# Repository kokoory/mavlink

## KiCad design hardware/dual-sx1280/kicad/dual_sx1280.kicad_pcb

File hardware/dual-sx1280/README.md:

# Dual SX1280 초소형 보드 (NiceRF LoRa1280 ×2 + STM32F103)

NiceRF **LoRa1280 시리즈 데모보드**(SX1280 ranging demo board)의 구성(LoRa1280 모듈 + 48핀 STM32 계열 MCU + 3~12 V 입력)을
기준으로, **SX1280 모듈 두 개를 동시에 쓰는 20 × 33 mm 4층 양면 보드**로 다시 설계한 것입니다.

## 사양
| 항목 | 내용 |
|---|---|
| 크기 | 20.0 × 33.0 mm, 4층, 1.0 mm 두께 권장 |
| 무선 | NiceRF LoRa1280 ×2 (SX1280, 2.4 GHz LoRa/FLRC/GFSK/레인징, 최대 12.5 dBm) |
| 배치 | 무선 A(U1) 윗면, 무선 B(U2) 아랫면, 같은 위치에 겹쳐 실장 |
| 안테나 | 무선마다 U.FL 1개 (J1 윗면, J2 아랫면), 50 Ω CPWG 약 2.4 mm |
| MCU | STM32F103CBU6 (UFQFPN48, 128 KB), 크리스털 없음(HSI) |
| 무선 연결 | A = SPI1, B = SPI2, 각각 NSS/BUSY/DIO1/NRESET 독립 → 두 무선 동시 동작 |
| 호스트 | J3 JST-SH 1.0 mm 4핀: 1 = +5 V, 2 = TX(PA9), 3 = RX(PA10), 4 = GND |
| 전원 | 5 V 입력 → AP2112K-3.3 (600 mA) |
| 펌웨어 기록 | 아랫면 SWD 패드(SWDIO/SWCLK/NRST/3V3/GND) 또는 BOOT0 패드 + USART1 ROM 부트로더 |
| 표시 | LED 2개(아랫면): PA12 녹색(무선 A), PA15 파랑(무선 B). PA15는 JTDI 겸용이라 펌웨어에서 JTAG을 끄고 SWD만 켜야 합니다(SWJ_CFG=010) |

핀 정의는 [firmware/board_pins.h](firmware/board_pins.h)에 있습니다.

### LoRa1280 핀 (16핀, 2.0 mm 피치 캐스텔레이션, 16 × 16 mm)
`1 DIO2 · 2 DIO3 · 3 VCC · 4 GND · 5 MISO · 6 MOSI · 7 SCK · 8 NSS · 9 ANT · 10–12 GND · 13 NRESET · 14 GND(TCXO판은 TCXOEN) · 15 BUSY · 16 DIO1`

### JP1 / JP2 (모듈 14번 핀)
- 기본값은 1-2 브리지(GND)이며, 일반 **LoRa1280 / LoRa1281** 모듈에 맞습니다.
- **LoRa1280-T(TCXO)** 모듈을 쓸 때만 1-2 사이를 칼로 끊고 2-3을 납땜합니다. 그러면 3V3이 들어가 TCXO가 켜집니다.
- 일반 모듈에서 2-3을 연결하면 3V3이 GND에 단락됩니다.

## 디렉터리
| 경로 | 내용 |
|---|---|
| `scripts/design.py` | **설계 원본**: 부품, 좌표, 넷. 여기만 고치고 나머지는 재생성 |
| `scripts/gen_lib.py`, `gen_sch.py`, `gen_pcb.py` | 라이브러리 / 회로도 / PCB(배치·존·RF) 생성 |
| `scripts/route.py` | 자체 A* 자동배선기 (F.Cu / In2.Cu / B.Cu) |
| `scripts/check_netlist.py`, `drc.py` | 회로도·PCB 넷 대조, KiCad DRC |
| `scripts/export_fab.py` | 거버, 드릴, JLCPCB BOM/CPL, 미리보기 이미지 |
| `kicad/` | KiCad 7 프로젝트 (`dual_sx1280.kicad_pro/.kicad_sch/.kicad_pcb`) |
| `fab/` | 제조 파일 |
| `docs/` | 회로도 PDF/PNG, 레이어 이미지, DRC 리포트 |

## 확인이 필요한 가정
1. **데모보드 MCU 품번은 확인하지 못했습니다.** 공개 사진에서는 48핀 QFP라는 것만 보입니다. 그래서 STM32F103 계열로 가정했습니다.
   - 같은 48핀 STM32F103C8T6/CBT6(LQFP)와 핀 번호가 같습니다. 풋프린트만 바꾸면 그대로 쓸 수 있습니다.
   - 정확한 MCU는 NiceRF 데모 코드(`Lora1280 lora1281 Demo code.rar`)나 판매처에 문의해 확인하세요.
2. **LoRa1280 핀맵과 외형**은 NiceRF LoRa128X 데이터시트 Rev 2.2의 핀 표와 TinyGS의 NiceRF-1280 보드를 교차 확인한 것입니다.
   - 발주 전에 실제 모듈 데이터시트의 기구 도면과 패드 치수를 꼭 대조하세요.
3. **모듈 아래에도 트랙과 텐트 비아가 지나갑니다.** 모두 솔더마스크로 덮여 있습니다.
   - 모듈 밑면에 캐스텔레이션 외의 노출 구리가 있다면 그 부분을 비워야 합니다.
4. LCSC 품번은 일부만 넣었습니다. 비어 있는 품번과 재고는 직접 확인해야 합니다. MCU, LED, 모듈이 해당합니다.
5. LoRa1280 모듈은 JLC 부품이 아니어서 수납땜해야 합니다. BOM과 CPL에서도 빠져 있습니다.

## 검증 결과 (2026-11-12)
| 검사 | 결과 |
|---|---|
| 회로도 넷리스트와 `design.py` 대조 (`check_netlist.py sch`) | PASS, 넷 31개 |
| PCB 넷과 `design.py` 대조 (`check_netlist.py pcb`) | PASS |
| KiCad DRC (`drc.py`, 보고서 `docs/drc_report.txt`) | 오류 0, 미연결 0, 경고 4 |
| 코트야드 겹침 (앞·뒷면 각각) | 0 |

- 경고 4건은 모두 `starved_thermal`입니다. 서멀 스포크가 1개만 붙은 GND 패드라는 뜻이고, 연결 자체는 되어 있습니다.
- 배선 통계는 트랙 약 620 mm, 비아 219개입니다. 비아 중 112개는 GND 스티칭 비아입니다.
- 회로도 ERC는 KiCad 7 CLI로 돌릴 수 없어서 하지 않았습니다. 대신 넷리스트를 1:1로 대조하고, 출력 핀 중복 같은 핀 타입 검사를 했습니다.
- 배선은 자동배선기 결과입니다. 발주 전에 KiCad에서 한 번 열어 육안으로 검토하길 권합니다. 특히 RF 주변, 전원 트랙 폭, 실크 위치를 보세요.

## 제조 (JLCPCB 기준)
- 4층, 1.0 mm, 외층 1 oz 기준입니다. 50 Ω 계산 근거는 L1-L2 프리프레그 7628 약 0.21 mm입니다.
- 최소 트랙과 간격은 0.15 / 0.15 mm, 비아는 0.45 / 0.25 mm입니다.
- `fab/dual_sx1280_gerbers.zip`, `fab/bom_jlcpcb.csv`, `fab/cpl_jlcpcb.csv`를 사용합니다.
- SMT 실장은 양면입니다. 윗면에는 MCU와 LDO, 아랫면에는 커넥터와 LED가 있습니다.
- CPL의 회전값은 KiCad 기준입니다. JLC 미리보기에서 U3, U4, J1~J3, LED의 방향을 꼭 확인하세요.
- 실크 일부(U2, J1, J2 표기)는 보드 밖에 걸쳐 있어 제조 시 잘립니다. 기능에는 영향이 없습니다.

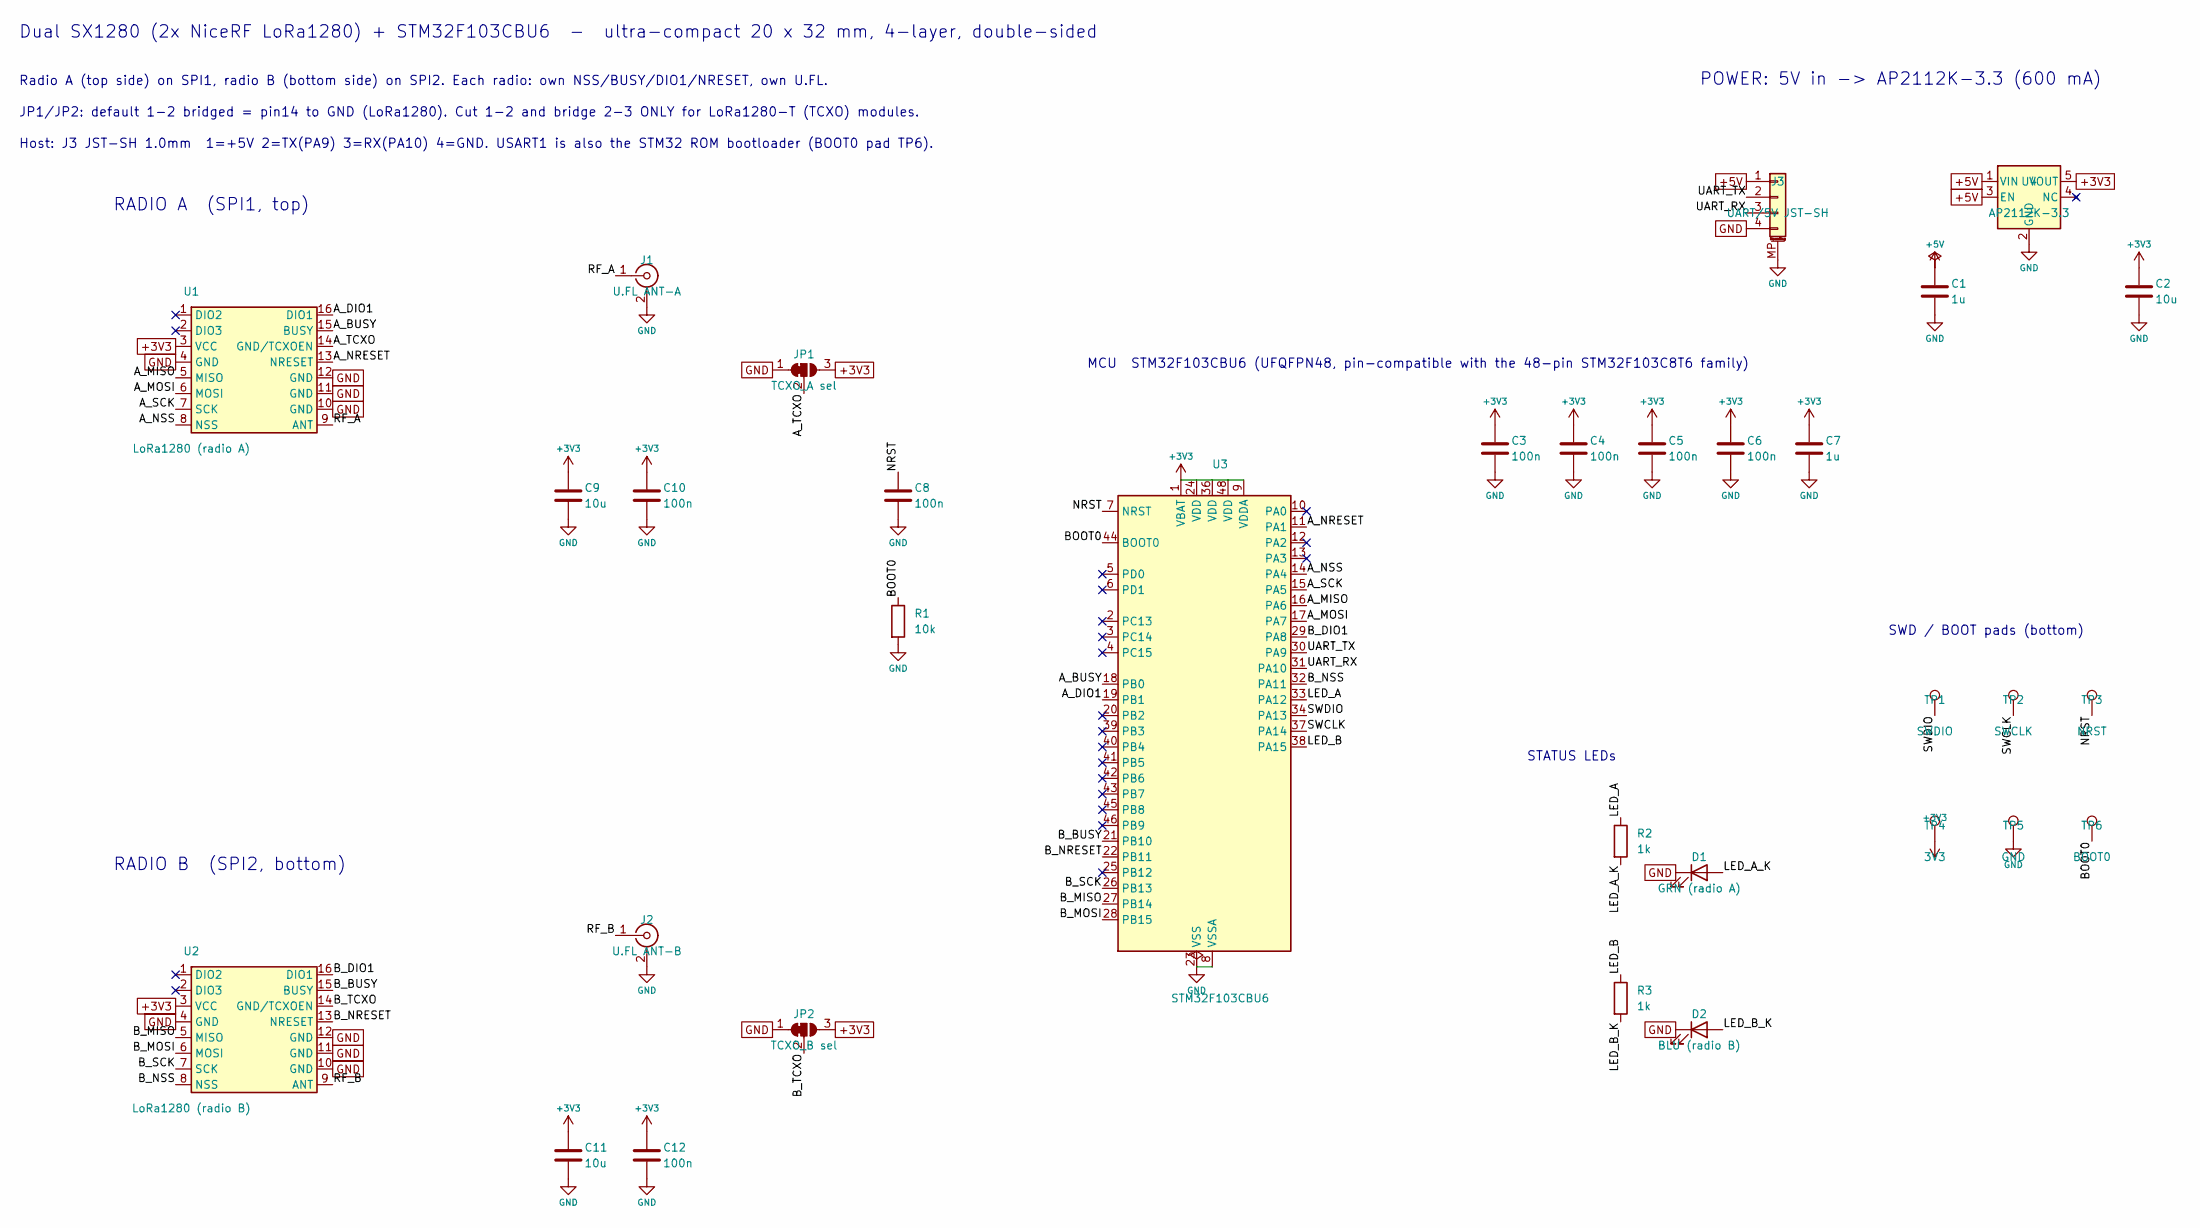
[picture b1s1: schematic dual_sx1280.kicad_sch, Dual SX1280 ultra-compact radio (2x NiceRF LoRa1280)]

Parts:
C1, C7: 1u; C_0402_1005Metric; MPN CL05A105KA5NQNC; LCSC C52923
C2, C9, C11: 10u; C_0603_1608Metric; MPN CL10A106KP8NNNC; LCSC C19702
C3, C4, C5, C6, C8, C10, C12: 100n; C_0402_1005Metric; MPN CL05B104KO5NNNC; LCSC C1525
D1: GRN (radio A); LED_0402_1005Metric; MPN 0402 green LED
D2: BLU (radio B); LED_0402_1005Metric; MPN 0402 blue LED
J1: U.FL ANT-A; U.FL_Hirose_U.FL-R-SMT-1_Vertical; MPN U.FL-R-SMT-1(10); LCSC C88374
J2: U.FL ANT-B; U.FL_Hirose_U.FL-R-SMT-1_Vertical; MPN U.FL-R-SMT-1(10); LCSC C88374
J3: UART/5V JST-SH; JST_SH_SM04B-SRSS-TB_1x04-1MP_P1.00mm_Horizontal; MPN SM04B-SRSS-TB(LF)(SN); LCSC C160404
JP1: TCXO_A sel; SolderJumper-3_P1.3mm_Bridged12_RoundedPad1.0x1.5mm
JP2: TCXO_B sel; SolderJumper-3_P1.3mm_Bridged12_RoundedPad1.0x1.5mm
R1: 10k; R_0402_1005Metric; MPN 0402WGF1002TCE; LCSC C25744
R2, R3: 1k; R_0402_1005Metric; MPN 0402WGF1001TCE; LCSC C11702
TP1: SWDIO; TestPoint_Pad_D1.0mm
TP2: SWCLK; TestPoint_Pad_D1.0mm
TP3: NRST; TestPoint_Pad_D1.0mm
TP4: 3V3; TestPoint_Pad_D1.0mm
TP5: GND; TestPoint_Pad_D1.0mm
TP6: BOOT0; TestPoint_Pad_D1.0mm
U1: LoRa1280 (radio A); NiceRF_LoRa1280_16x16mm; MPN NiceRF LoRa1280
U2: LoRa1280 (radio B); NiceRF_LoRa1280_16x16mm; MPN NiceRF LoRa1280
U3: STM32F103CBU6; QFN-48-1EP_7x7mm_P0.5mm_EP5.6x5.6mm; MPN STM32F103CBU6
U4: AP2112K-3.3; SOT-23-5; MPN AP2112K-3.3TRG1; LCSC C51118

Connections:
+3V3: C2.1, C3.1, C4.1, C5.1, C6.1, C7.1, C9.1, C10.1, C11.1, C12.1, JP1.3 (B), JP2.3 (B), TP4.1, U1.3 (VCC), U2.3 (VCC), U3.1 (VBAT), U3.9 (VDDA), U3.24 (VDD), U3.36 (VDD), U3.48 (VDD), U4.5 (VOUT)
+5V: C1.1, J3.1, U4.1 (VIN), U4.3 (EN)
A_BUSY: U1.15 (BUSY), U3.18 (PB0)
A_DIO1: U1.16 (DIO1), U3.19 (PB1)
A_MISO: U1.5 (MISO), U3.16 (PA6)
A_MOSI: U1.6 (MOSI), U3.17 (PA7)
A_NRESET: U1.13 (NRESET), U3.11 (PA1)
A_NSS: U1.8 (NSS), U3.14 (PA4)
A_SCK: U1.7 (SCK), U3.15 (PA5)
A_TCXO: JP1.2 (C), U1.14 (GND/TCXOEN)
BOOT0: R1.1, TP6.1, U3.44 (BOOT0)
B_BUSY: U2.15 (BUSY), U3.21 (PB10)
B_DIO1: U2.16 (DIO1), U3.29 (PA8)
B_MISO: U2.5 (MISO), U3.27 (PB14)
B_MOSI: U2.6 (MOSI), U3.28 (PB15)
B_NRESET: U2.13 (NRESET), U3.22 (PB11)
B_NSS: U2.8 (NSS), U3.32 (PA11)
B_SCK: U2.7 (SCK), U3.26 (PB13)
B_TCXO: JP2.2 (C), U2.14 (GND/TCXOEN)
GND: C1.2, C2.2, C3.2, C4.2, C5.2, C6.2, C7.2, C8.2, C9.2, C10.2, C11.2, C12.2, D1.1 (K), D2.1 (K), J1.2 (Ext), J2.2 (Ext), J3.4, J3.MP (MountPin), JP1.1 (A), JP2.1 (A), R1.2, TP5.1, U1.4 (GND), U1.10 (GND), U1.11 (GND), U1.12 (GND), U2.4 (GND), U2.10 (GND), U2.11 (GND), U2.12 (GND), U3.8 (VSSA), U3.23 (VSS), U3.35 (VSS), U3.47 (VSS), U3.49 (VSS), U4.2 (GND)
LED_A: R2.1, U3.33 (PA12)
LED_A_K: D1.2 (A), R2.2
LED_B: R3.1, U3.38 (PA15)
LED_B_K: D2.2 (A), R3.2
NRST: C8.1, TP3.1, U3.7 (NRST)
RF_A: J1.1 (In), U1.9 (ANT)
RF_B: J2.1 (In), U2.9 (ANT)
SWCLK: TP2.1, U3.37 (PA14)
SWDIO: TP1.1, U3.34 (PA13)
UART_RX: J3.3, U3.31 (PA10)
UART_TX: J3.2, U3.30 (PA9)

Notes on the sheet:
Dual SX1280 (2x NiceRF LoRa1280) + STM32F103CBU6 - ultra-compact 20 x 32 mm, 4-layer, double-sided
Radio A (top side) on SPI1, radio B (bottom side) on SPI2. Each radio: own NSS/BUSY/DIO1/NRESET, own U.FL.
JP1/JP2: default 1-2 bridged = pin14 to GND (LoRa1280). Cut 1-2 and bridge 2-3 ONLY for LoRa1280-T (TCXO) modules.
Host: J3 JST-SH 1.0mm 1=+5V 2=TX(PA9) 3=RX(PA10) 4=GND. USART1 is also the STM32 ROM bootloader (BOOT0 pad TP6).
RADIO A (SPI1, top)
RADIO B (SPI2, bottom)
MCU STM32F103CBU6 (UFQFPN48, pin-compatible with the 48-pin STM32F103C8T6 family)
POWER: 5V in -> AP2112K-3.3 (600 mA)
SWD / BOOT pads (bottom)
STATUS LEDs

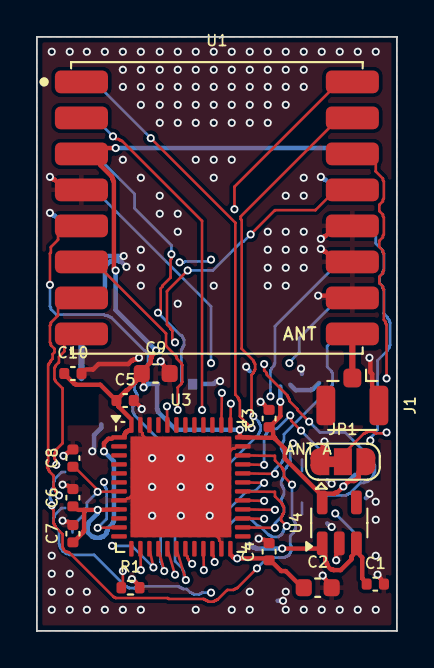
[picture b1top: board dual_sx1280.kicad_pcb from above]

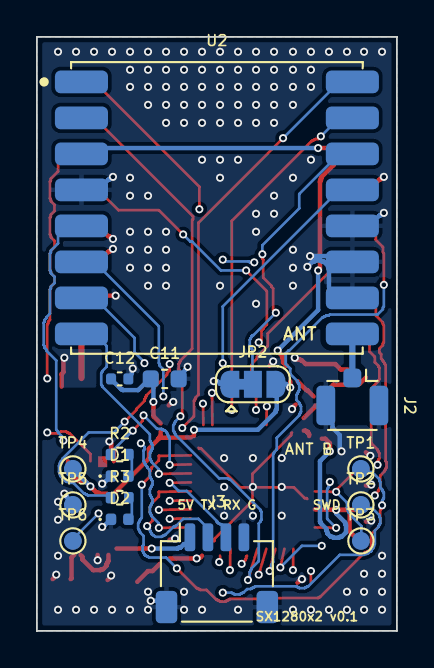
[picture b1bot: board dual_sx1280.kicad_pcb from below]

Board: 4 copper layers, 20.0 x 33.0 mm, 32 parts (16 on the bottom side), 31 nets.

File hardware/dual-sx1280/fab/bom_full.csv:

Qty,Designators,Value,Footprint,MPN,LCSC,Assembly
2,C1 C7,1u,C_0402_1005Metric,CL05A105KA5NQNC,C52923,SMT
3,C11 C2 C9,10u,C_0603_1608Metric,CL10A106KP8NNNC,C19702,SMT
7,C10 C12 C3 C4 C5 C6 C8,100n,C_0402_1005Metric,CL05B104KO5NNNC,C1525,SMT
1,D1,GRN,LED_0402_1005Metric,0402 green LED,,SMT
1,D2,BLU,LED_0402_1005Metric,0402 blue LED,,SMT
1,J1,U.FL ANT-A,U.FL_Hirose_U.FL-R-SMT-1_Vertical,U.FL-R-SMT-1(10),C88374,SMT
1,J2,U.FL ANT-B,U.FL_Hirose_U.FL-R-SMT-1_Vertical,U.FL-R-SMT-1(10),C88374,SMT
1,J3,UART/5V JST-SH,JST_SH_SM04B-SRSS-TB_1x04-1MP_P1.00mm_Horizontal,SM04B-SRSS-TB(LF)(SN),C160404,SMT
1,JP1,TCXO_A sel,SolderJumper-3_P1.3mm_Bridged12_RoundedPad1.0x1.5mm,,,not a part (pad)
1,JP2,TCXO_B sel,SolderJumper-3_P1.3mm_Bridged12_RoundedPad1.0x1.5mm,,,not a part (pad)
1,R1,10k,R_0402_1005Metric,0402WGF1002TCE,C25744,SMT
2,R2 R3,1k,R_0402_1005Metric,0402WGF1001TCE,C11702,SMT
1,TP1,SWDIO,TestPoint_Pad_D1.0mm,,,not a part (pad)
1,TP2,SWCLK,TestPoint_Pad_D1.0mm,,,not a part (pad)
1,TP3,NRST,TestPoint_Pad_D1.0mm,,,not a part (pad)
1,TP4,3V3,TestPoint_Pad_D1.0mm,,,not a part (pad)
1,TP5,GND,TestPoint_Pad_D1.0mm,,,not a part (pad)
1,TP6,BOOT0,TestPoint_Pad_D1.0mm,,,not a part (pad)
2,U1 U2,LoRa1280,NiceRF_LoRa1280_16x16mm,NiceRF LoRa1280,,hand-solder
1,U3,STM32F103CBU6,QFN-48-1EP_7x7mm_P0.5mm_EP5.6x5.6mm,STM32F103CBU6,,SMT
1,U4,AP2112K-3.3,SOT-23-5,AP2112K-3.3TRG1,C51118,SMT

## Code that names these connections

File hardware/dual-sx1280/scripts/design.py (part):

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    "SWDIO":   ["U3.34", "TP1.1"],
    "SWCLK":   ["U3.37", "TP2.1"],
    # host UART (USART1, also the STM32 ROM bootloader port)
    "UART_TX": ["U3.30", "J3.2"],   # PA9  -> host RX
    "UART_RX": ["U3.31", "J3.3"],   # PA10 <- host TX
    # LEDs
    "LED_A":   ["U3.33", "R2.1"],   # PA12
    "LED_A_K": ["R2.2", "D1.2"],
    "LED_B":   ["U3.38", "R3.1"],   # PA15 (JTDI: use SWD-only remap)
    "LED_B_K": ["R3.2", "D2.2"],
    # Radio A on SPI1
    "A_NSS":    ["U3.14", "U1.8"],   # PA4
    "A_SCK":    ["U3.15", "U1.7"],   # PA5 SPI1_SCK
    "A_MISO":   ["U3.16", "U1.5"],   # PA6 SPI1_MISO
    "A_MOSI":   ["U3.17", "U1.6"],   # PA7 SPI1_MOSI
    "A_BUSY":   ["U3.18", "U1.15"],  # PB0
    "A_DIO1":   ["U3.19", "U1.16"],  # PB1  (EXTI1)
    "A_NRESET": ["U3.11", "U1.13"],  # PA1
    "A_TCXO":   ["U1.14", "JP1.2"],
    "RF_A":     ["U1.9", "J1.1"],
    # Radio B on SPI2
    "B_NSS":    ["U3.32", "U2.8"],   # PA11 (software NSS)
    "B_SCK":    ["U3.26", "U2.7"],   # PB13 SPI2_SCK
    "B_MISO":   ["U3.27", "U2.5"],   # PB14 SPI2_MISO
    "B_MOSI":   ["U3.28", "U2.6"],   # PB15 SPI2_MOSI
    "B_BUSY":   ["U3.21", "U2.15"],  # PB10
    "B_DIO1":   ["U3.29", "U2.16"],  # PA8  (EXTI8)
    "B_NRESET": ["U3.22", "U2.13"],  # PB11
    "B_TCXO":   ["U2.14", "JP2.2"],
    "RF_B":     ["U2.9", "J2.1"],
}
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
